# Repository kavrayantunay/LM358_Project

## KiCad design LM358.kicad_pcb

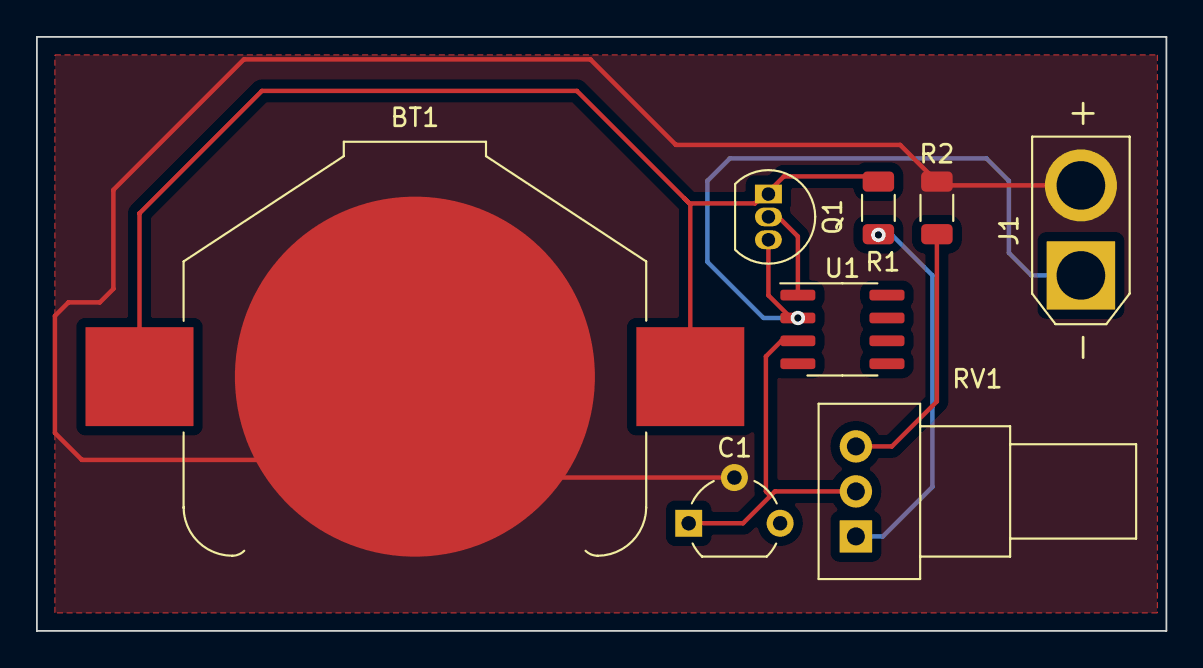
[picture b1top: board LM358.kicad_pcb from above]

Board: 2 copper layers, 62.8 x 33.0 mm, 8 parts (0 on the bottom side), 7 nets.

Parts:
BT1: 9V; BatteryHolder_Keystone_3008_1x2450
C1: 100nF; TO-92_Wide
J1: klemens; AMASS_XT30U-F_1x02_P5.0mm_Vertical
Q1: BC547; TO-92_Inline
R1, R2: 100R; R_1206_3216Metric
RV1: 10K; Potentiometer_Alps_RK09Y11_Single_Horizontal
U1: LM358; SOIC-8_3.9x4.9mm_P1.27mm

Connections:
GND: BT1.2 (-), C1.2, J1.2 (GND), R2.2
unnamed: BT1.1 (+), Q1.1 (C), R1.1
unnamed: C1.1, RV1.2, U1.3 (+)
unnamed: J1.1 (Vcc), Q1.3 (E), U1.2 (-)
unnamed: Q1.2 (B), U1.1
unnamed: R1.2, RV1.1
unnamed: R2.1, RV1.3
